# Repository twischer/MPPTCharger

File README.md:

# MPPTCharger
Maximum Power Point Tracking Charge Controller for ESP8266 and Raspberry Pi

## Setup build system
```bash
sudo apt install python3-pip
sudo pip3 install platformio
```

## Building for ESP8266
```bash
cd source
pio run -t upload
```

## Building for Raspberry Pi
Only supported to build natively on Raspberry Pi
```bash
cd rpi
pio run
.pio/build/raspberrypi_3b/program

```

### Enable I2C driver
```
$ vi /boot/config.txt
dtparam=i2c_arm=on
```

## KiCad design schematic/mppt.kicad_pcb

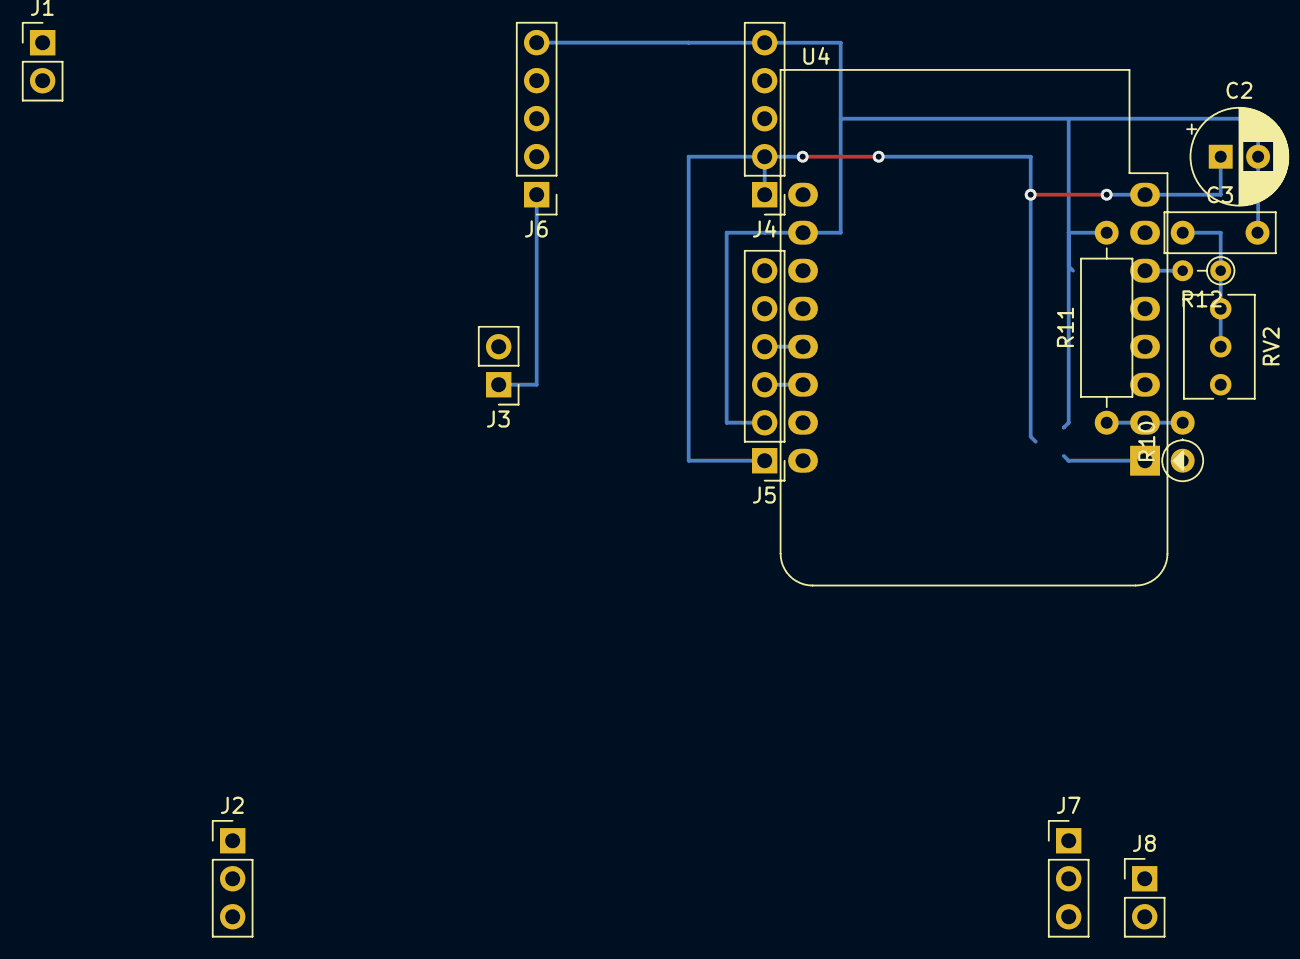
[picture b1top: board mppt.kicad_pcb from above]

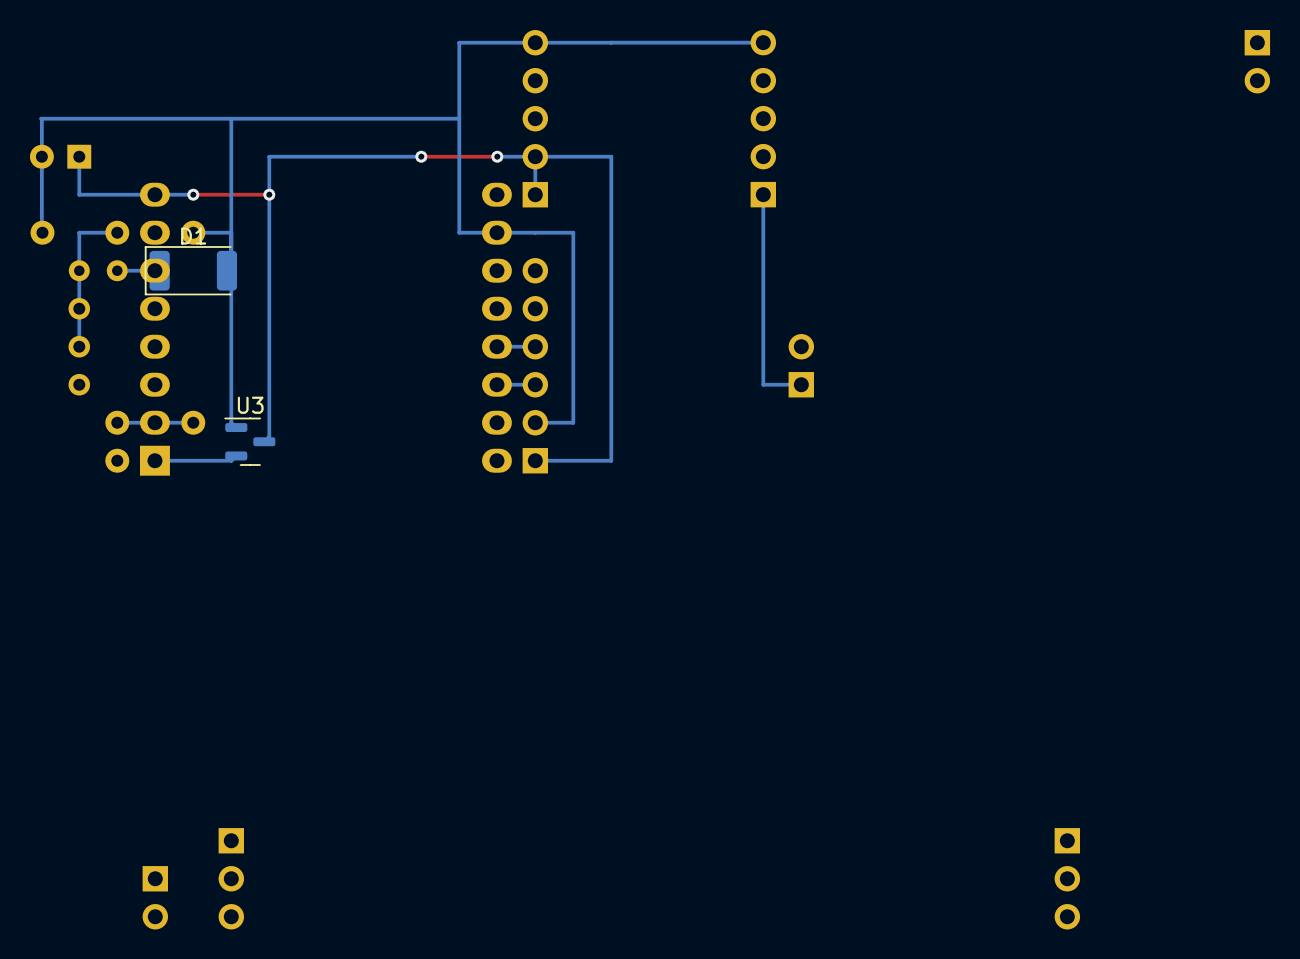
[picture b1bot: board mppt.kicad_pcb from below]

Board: 2 copper layers, 17 parts (2 on the bottom side), 12 nets.

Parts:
C2: 100µ; CP_Radial_D6.3mm_P2.50mm
C3: 1µ; C_Rect_L7.2mm_W2.5mm_P5.00mm_FKS2_FKP2_MKS2_MKP2
D1: 3V6; D_2010_5025Metric
J1: Solar; PinHeader_1x02_P2.54mm_Vertical
J2: TL494-IN; PinHeader_1x03_P2.54mm_Vertical
J3: INA219; PinHeader_1x02_P2.54mm_Vertical
J4: MP2307-OUT; PinHeader_1x05_P2.54mm_Vertical
J5: INA219; PinHeader_1x06_P2.54mm_Vertical
J6: MP2307-IN; PinHeader_1x05_P2.54mm_Vertical
J7: TL494-OUT-42V-3A; PinHeader_1x03_P2.54mm_Vertical
J8: LiIon-36V; PinHeader_1x02_P2.54mm_Vertical
R10: 120k; R_Axial_DIN0207_L6.3mm_D2.5mm_P2.54mm_Vertical
R11: 2k2; R_Axial_DIN0309_L9.0mm_D3.2mm_P12.70mm_Horizontal
R12: 1k2; R_Axial_DIN0204_L3.6mm_D1.6mm_P2.54mm_Vertical
RV2: 10k; Potentiometer_Bourns_3266Y_Vertical
U3: MAX809S; SOT-23
U4: WeMos_D1_mini; WEMOS_D1_mini_light

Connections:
GND: C2.2, C3.2, D1.2 (A), J1.1, J2.3, J4.5, J5.2, J6.5, R11.2, U3.1 (GND), U4.10 (GND)
unnamed: C2.1, J4.1, J4.2, J5.1, U3.3 (VCC), U4.8 (3V3)
unnamed: C3.1, R12.1, RV2.2, RV2.3
unnamed: D1.1 (K), R12.2, U4.6 (MOSI/D7)
unnamed: J7.1, R10.1
unnamed: J1.2, J3.2, J5.6
unnamed: J2.1, J3.1, J5.5, J6.1
unnamed: J5.3, U4.14 (SCL/D1)
unnamed: J5.4, U4.13 (SDA/D2)
unnamed: J7.3, J8.2
unnamed: R10.2, R11.1, U4.2 (A0)
unnamed: U3.2 (RESET), U4.1 (~RST)

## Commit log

2020-11-02 Add schematic and basic source
2020-11-02 ADCReader: Always add offset to ADC values
2020-11-02 Add maximal power point tracking algo
2020-11-02 Provide class to calculate power and energy
2020-11-02 mppt: Use right sigma delta channel for attaching
2020-11-04 mppt: Use min sigma delta freqency of 156kHz
    In case of 312,5kHz the worst case frequency can be up to 40MHz.
    This seams to crash the ESP. At least the telnet session is not updating
    anymore
2020-11-04 Non negativ charge level and PWM level
2020-11-04 adc: Set offsets
2020-11-04 schematic: Use rsistor for DTC connection to limit current to TL494 capacitor
2020-11-06 mppt: Deside new direction depending on old direction
2020-11-07 ycm: Adapt header file pathes
2020-11-07 Wait for Avarage and print after desition
2020-11-07 mppt: remeber maxima until smaller threshold
2020-11-07 ToBeVerified: Use avarage instead of median
2021-01-05 adc: capture 16 samples per channel before moving to next channel
2021-01-05 schematic: Add 100nF capacitors
2021-01-05 adc: calucalte in float and avarage
2021-01-05 Do not use median
2021-01-05 mppt: cluclate in float
2021-01-05 Remove simple IIR
2021-01-05 make printing faster
2021-01-05 adcclacl: caluclate everything in float
2021-01-05 Print PWM direction
2021-01-05 mppt: Add 3% + 1W hysteresis
2021-01-05 Update screen faster but slow down measurmeents
2021-01-05 Add SW watchdog only triggered after print
    Ensures that ESP woudl reset in case anything up to Print is not working
2021-01-05 Disable TL494 already before initializing WiFi
    >32ms (=61ms-28ms) before initializing MPPT
2021-01-05 wifi: Do not block in captive portal
    when STA not available
2021-01-05 fixup! adcclacl: caluclate everything in float
2021-01-05 Include ina219 library
2021-01-05 Use ArduinoINA219
2021-01-05 schematic: Use INA219
2021-01-05 mppt: Allow search window of 0.1W
2021-01-05 telnet: Sent one page as one TCP package
2021-01-05 mppt: Reduce max sigma delta to 5MHz
2021-01-05 Add GDB stub
2021-01-05 adc: Adapt out voltage to max charge voltage
    messearued by Fluke multimeter.
    100mV underneath max charge voltage.
    ADC value before this patch: 41,76V
    Mesured by Fluke multimeter: 41,9V
2021-01-05 Swap GPIO0 and GPIO13
2021-01-05 schematic: Reduce GPIO15 pull down to 2,2kOhm
2021-01-05 Switch step up of when output voltage exceeds max + 1%
2021-01-05 ADCCalc: Remove it
    not longer required when using INA
2021-01-05 ina219calc: Calculate and print the energy
2021-01-05 Print up time of ESP8266
2021-01-07 Optimize for slower AP mode
2021-01-07 watchdog: Disbale it when starting web portal
2021-04-17 schematic: Supply ESP from battery
    When the ESP is supplied by the solar panel it starts quite late on
    raising sun. As long as the ESP is not running the step up converter is
    running. It drains so much power that the supply voltage for the ESP is
    to low.
2021-04-29 readme: Describe build steps
2021-04-29 Add Raspberry Pi 3b build target
2021-04-29 Provide Arduino lib dependencies
2021-04-29 Implement variant handling
2021-04-29 fixup! Provide Arduino lib dependencies
2021-04-29 fixup! Add Raspberry Pi 3b build target
2021-04-29 Workaround: Disable Arduino Filters for LDF
    TODO check why LDF still includes thse files
2021-05-05 rpi: Initial pio project
2021-05-05 rpi: Provide makefile for compiling
    with qemu and change root
2021-05-07 fixup! readme: Describe build steps
2021-05-07 mppt: Extract as a library
2021-05-07 rpi: Include MPPT
2021-05-07 mppt: Provide different output impementations
2021-05-07 rpi: Use MPPT PWM output implementation
2021-05-12 fixup! rpi: Use MPPT PWM output implementation
2021-05-12 rpi enable INA219 driver
2021-05-13 schematic: Add rpi wiring
2021-05-18 enable ina219
2021-05-18 print ina219 values
2021-05-18 Read voltage and power from stdin
2021-12-27 Support d1 Mini board
2021-12-27 Remove TelnetStream2 include
2022-03-06 sch: Use error amp of TL494 for MPPT
2022-03-30 Extract MPPT lib
